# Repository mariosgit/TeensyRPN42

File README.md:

# What ???

Trying to compile Free42 on a Teensy4 / STM32F4xx.

It's a PlatformIO project, copied some code from free42 into lib and trying to compile it...

Allmost, just some link references to open/unlink/link file operations triggered from somethere ???

# Status

Ultraexperimental.

Works with double precision over terminal.

```
╒══════════════════════════════════════════════════════════════════════════════════════════════════════════════════╕
│                                                                                                                  │
│                                                                                                                  │
│             ▄▀▀▀▄       ▄▀▀▀▄ ▄▀▀▀▄ ▄▀▀▀▄ ▀▀▀▀█  ▄█   ▀▀▀▀█ ▄▀▀▀▄   ▄█  ▀▀▀▀█ ▄▀▀▀▄ ▄▀▀▀▄ ▄▄▄▄         ▄█        │
│ ▀▄ ▄▀ ▄       ▄▄▀       ▀▄▄▄█   ▄▄▀  ▄▄▄▀   ▄▀    █     ▄▀  █ ▄▀█ ▄▀ █    ▄▀    ▄▄▀  ▄▄▄▀ █▄▄   ▄▄▄▄    █        │
│   █   ▄     ▄▀     ▄▄      ▄▀ ▄▀    ▄   █  █      █    █    █▀  █ ▀▀▀█▀  █    ▄▀    ▄   █ █▄▄▄          █        │
│   ▀         ▀▀▀▀▀  ▀▀    ▀▀   ▀▀▀▀▀  ▀▀▀   ▀     ▀▀▀   ▀     ▀▀▀     ▀   ▀    ▀▀▀▀▀  ▀▀▀               ▀▀▀       │
│                    ▄█         ▀▀▀▀█ █▀▀▀▀  ▄▀▀  ▄▀▀▀▄ ▀▀▀▀█ ▄▀▀▀▄ █▀▀▀▀ █▀▀▀▀ ▄▀▀▀▄  ▄█   ▀▀▀▀█ ▄▄▄▄         ▄█  │
│ ▀▄ ▄▀ ▄     ▄▄▄▄    █           ▄▀  ▀▀▀▀▄ █▄▄▄   ▄▄▄▀   ▄▀   ▄▄▄▀ ▀▀▀▀▄ ▀▀▀▀▄ ▀▄▄▄▀   █     ▄▀  █▄▄   ▄▄▄▄    █  │
│  ▄▀▄  ▄             █    ▄▄    █    ▄   █ █   █ ▄   █  █    ▄   █ ▄   █ ▄   █ █   █   █    █    █▄▄▄          █  │
│ ▀   ▀              ▀▀▀   ▀▀    ▀     ▀▀▀   ▀▀▀   ▀▀▀   ▀     ▀▀▀   ▀▀▀   ▀▀▀   ▀▀▀   ▀▀▀   ▀                 ▀▀▀ │
╘══════════════════════════════════════════════════════════════════════════════════════════════════════════════════╛
```

# Software

* replaced scanf %e %g with own parser.
  * Todo: PIO_FRAMEWORK_ARDUINO_NANOLIB_FLOAT_SCANF ([from platformio stm32 page](https://docs.platformio.org/en/latest/platforms/ststm32.html))

* quad precission ?
  * checking free42(swissmicro build process..)
    * gcc111libbid-arm64.a - lib src is packaged with it. And available on github
    * there is scanf stuff in ```common/core_phloat.cc``` only when not ARM build ?
    * cmd line:
    ```
    arm-none-eabi-g++ -Os -DDM42_OLDHW -I../common -DRELEASE -MMD -Wall -Wno-misleading-indentation -Wno-parentheses -Wno-write-strings -Wno-maybe-uninitialized -Wno-unknown-pragmas -Wno-class-memaccess -Wno-sign-compare -fno-exceptions -fno-rtti -DVERSION="\"3.3.8\"" -DDECIMAL_CALL_BY_REFERENCE=1 -DDECIMAL_GLOBAL_ROUNDING=1 -DDECIMAL_GLOBAL_ROUNDING_ACCESS_FUNCTIONS=1 -DDECIMAL_GLOBAL_EXCEPTION_FLAGS=1 -DDECIMAL_GLOBAL_EXCEPTION_FLAGS_ACCESS_FUNCTIONS=1 -D_WCHAR_T_DEFINED  -fdata-sections -ffunction-sections -Wl,--gc-sections -ggdb -mthumb -march=armv7e-m -mfloat-abi=hard -mfpu=fpv4-sp-d16 -DARM -DBCD_MATH -c -o core_phloat.o ../common/core_phloat.cc
    ```

  * It builds with the intel lib but it's a bit (way too) large
    ```
    ld: region `RAM' overflowed by 798408 bytes
    ld: region `FLASH' overflowed by 2006716 bytes
    ```

# Hardware

Ideas...

* STM32 ? Nucleo-F411RE - is dev board 
  ```
  RAM:   [=         ]   9.7% (used 12704 bytes from 131072 bytes)
  Flash: [======    ]  62.7% (used 328636 bytes from 524288 bytes)
  ```
  Connect other board to Nucleo STLink programmer part:
  * Remove SB13/SB14 for TX/RX connection to Nucleo MCU
  * Connect SWD (SWO not needed) (Open Jumpers to Nucleo MCU)
  * Connect TX->RX Rx->TX

  Alternative ? L432KC ?
* Display ???
  * OLED ? 256x64
* Keys 
  * K.Choc low profile mechaniks
* Power ?
  * Single Lipo ? Cheap Charger...

## PCB Ordered 

commit: 9db91b7e23bbdf1880c24b6f514a0bee10d9d54c

## Costa ?

| What | Where | $$$ |
|---|---|---:|
| PCB | JLC 5x | 27/5 = 5.4 |
| OLED "OLED Display 2.8" 256*64" | AliEx | 22 |
| Keith Choc V1 | AliEx | ~30 |
| LEDs "WS2812 2020" 500x | AliEx | 22/13 = 1.7 |
| BOM all | Reichelt | 20 |
| **Sum** | | ~100 |

# Refs

thomasokken's ingenious https://thomasokken.com/free42 https://github.com/aswild/free42

And code on github: https://github.com/swissmicros/free42

OpenRPNCalc ? on github, uses CubeIDE 🤯 and own code..

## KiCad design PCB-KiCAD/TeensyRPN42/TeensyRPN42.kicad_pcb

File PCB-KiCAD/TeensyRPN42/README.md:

# TeensyRPN42 – PCB

Main board for an RPN calculator running [Free42](https://thomasokken.com/free42/) on an STM32F405.
37 Kailh Choc V1 keys, each with an SK6805 RGB LED in the key window, a 2.8" 256×64 SPI OLED, and a LiPo
supply with a switchable 5 V boost for the LEDs. Two layers; all parts on the top side except the SWD (J1) and serial (J4) headers.

| Front | Headers | Back |
|---|---|---|
|  |  |  |
|  | |  |

**Interactive BOM:** [bom/TeensyRPN42_ibom.html](bom/TeensyRPN42_ibom.html) (open in a browser; placement per part, with Reichelt numbers).

## Specs

| | |
|---|---|
| Board | 113.0 × 184.1 mm, 3 mm corner radius, 2 layers, 4 × M3 mounting holes (3.7 mm, tolerance for the OLED module) |
| Fab | AISLER 2-layer simple (min. track 0.2 mm, clearance 0.15 mm, via 0.7/0.3 mm), vias tented |
| MCU | STM32F405RGT6 (LQFP64), 8 MHz HSE (Y3, ceramic 5.2 × 3.4 mm), 32.768 kHz LSE (Y2) for the RTC |
| Display | 2.8" OLED module, 16-pin header J3, SPI1 |
| Keys | 37 × Choc V1 (1u / 1.25u / 2u ENTER), 7 × 6 matrix, no diodes |
| LEDs | 38 × SK6805 2020 (2 × 2 mm, on the 2427 footprint; two under the 2u ENTER), one data chain, 5 V via 74AHCT125 level shifter |
| Power | 1-cell LiPo through an off-board TP4056 + DW01 module (J5 BAT, J9 CHG Vusb) |
| 3.3 V | MCP1727-3302 LDO from the battery (MCU, OLED) |
| 5 V | TS1935BCX5 boost (2.6–5.5 V in, 1.9 A switch), switched by PC3 through a P-FET load switch |
| USB | Micro-USB (J7), USB FS on PA11/PA12, USBLC6 ESD, 750 mA PTC, SMAJ5.0A TVS |
| Programming | USB DFU (BOOT0 button / jumper), SWD (J1) |

## Connectors

| Ref | Side | Pins |
|---|---|---|
| J1 SWD | back | 1 3V3 (VTref) · 2 SWCLK · 3 GND · 4 SWDIO · 5 NRST · 6 SWO |
| J4 Serial | back | GND · TX (PA2) · RX (PA3), 3.3 V, 115200 baud |
| J5 BAT | top edge | 1 GND · 2 PWR_SYS ← TP4056 module OUT+/OUT− (never B−) |
| J9 CHG Vusb | top edge | 1 GND · 2 VBUS → TP4056 module IN+/IN− |
| J10 BOOT0 | top | jumper = BOOT0 to 3.3 V → every reset lands in DFU |
| J2 / J8 | top | I²C1: PB8 SCL, PB9 SDA, 2.2 k pull-ups (mini OLED / spare) |
| J3 | top | 2.8" OLED module (SPI1) |
| J7 | top edge | Micro-USB (data + charging) |
| SW1 / SW2 | top (right / left edge) | RESET / BOOT0 |

## MCU pin map

| Function | Pins |
|---|---|
| Matrix rows 1…7 | PA9, PA10, PD2, PC12, PC11, PC10, PA15 |
| Matrix columns 0…5 | PC7, PC8, PC9, PB5, PB6, PB7 (inputs, pull-up) |
| OLED (SPI1) | PA5 SCK, PA7 MOSI, PA4 CS, PC4 D/C, RESET = NRST |
| LED data | PB10 → 74AHCT125 → 470 Ω → D1 … D38 |
| I²C1 | PB8 SCL, PB9 SDA |
| USART2 | PA2 TX, PA3 RX |
| USB FS | PA11 D−, PA12 D+ (VBUS sensing off, PA9 is ROW1) |
| SWD | PA13 SWDIO, PA14 SWCLK, PB3 SWO |
| VBUS_DET | PA1, 100 k / 150 k divider → ≈ 3.0 V with USB |
| BAT_SENSE | PA0, 200 k / 200 k divider → V_bat / 2 |
| BOOST_EN | PC3, high = 5 V on (100 k pull-down, off during reset) |
| BOOT0 / BOOT1 | BOOT0 10 k pull-down (SW2 / J10 → 3.3 V), PB2 10 k pull-down |
| Spare | PA8, PB0, PB1, PB4, PB11, PB12–PB15, PC0, PC1, PC2, PC5, PC6, PC13 |

## BOM

Full BOM with your Part-DB stock and the Reichelt order list: **[bom/BOM.md](bom/BOM.md)**.

- Resistors, 100 nF, 1 nF, 18 pF, the STM32F405 and the OLED come from stock.
- Reichelt: 22 positions, about 8.60 € (ICs, FETs, ferrites, 22 µF, PTC, TVS, Schottky, crystal Y3 (IC14M8), DTSM-61K, MIC USB BBU, headers).
- L4: Reichelt `L-242418FPS 6,3µ` (6.3 µH, Isat 3.8 A) on the SRP5030 pads; L5 (DNP) is a parallel 10 × 10 mm footprint for the stock SRU1048-100Y.
- Elsewhere: Y2 (32.768 kHz 3215, CL 6–7 pF), 38 SK6805 2020 LEDs (ordered).
- Own stock: 37 Kailh Choc V1 switches; keycaps are 3D printed (`KeycapsForKailhChoc-files/`).

**DNP (footprint only):** L5 (10 × 10 mm alternative to L4), Y1 (alternative 8 MHz HC49 footprint),
Y4 (alternative 32.768 kHz footprint, fits the Reichelt IQD LFXTAL003000).
**Off-board:** TP4056 + DW01 charger module (set R_PROG to 2.4 k ≈ 500 mA), 1-cell LiPo.

## Design notes

- **Power path:** battery → module OUT+ → J5 → PWR_SYS. PWR_SYS feeds the LDO (always on) and the boost
  through Q1. BOOST_EN (PC3) high → Q2 pulls Q1's gate low → BOOST_IN = battery → U5 starts → +5 V.
  R24 10 k + C56 100 nF slow Q1's turn-on to ≈ 0.9 ms (inrush into the 5 V / LED caps).
  Q1 is needed because a non-synchronous boost always conducts battery → L4 → D42 → +5 V; without it the
  LEDs would draw idle current in soft-off.
- **5 V budget:** ≈ 0.6 A at 5 V from a 3.0 V battery. Limit LED brightness in firmware (total LED current
  ≲ 0.5 A). Soft-off / low-battery warning at ≈ 3.4 V (BAT_SENSE); the DW01 only cuts at ≈ 2.5 V.
- **V-LED:** separate branch behind ferrite L3 with C53 22 µF at the feed point and 24 × 100 nF spread along the rows.
  Ladder layout: one trunk on each side, one bus per key row, so most rows are fed from both ends.
- **Filtering:** L1 + C6/C30 for VDDA, L2 + C13 for the OLED supply.
- **Key matrix (no diodes):** drive only the active row low, all other rows hi-Z; columns are inputs with
  pull-ups. One or two keys at a time are reliable; ghosting needs three or more held keys.
- **DFU:** hold BOOT0 (SW2), tap RESET (SW1), release. During development, a jumper on J10 keeps the board
  in DFU after every reset. `dfu-util -a 0 -s 0x08000000:leave -D firmware.bin`.
- **Clock:** use HSE 8 MHz → PLL 168 MHz (PLLM 8, PLLN 336, PLLP 2, PLLQ 7 = 48 MHz USB); HSI is not
  accurate enough for USB.
- **Fixed mechanics:** OLED J3, the 37 switches, H1–H4 and the outline are locked;
  `python3 check_fixed.py` verifies them against `fixed_placement.json`.
- **DRC:** clean. The LED-in-switch courtyard overlaps (intended) and H3/H4 vs J3 are excluded. Footprint
  library-mismatch warnings are local edits (silk tweaks) and intentional.

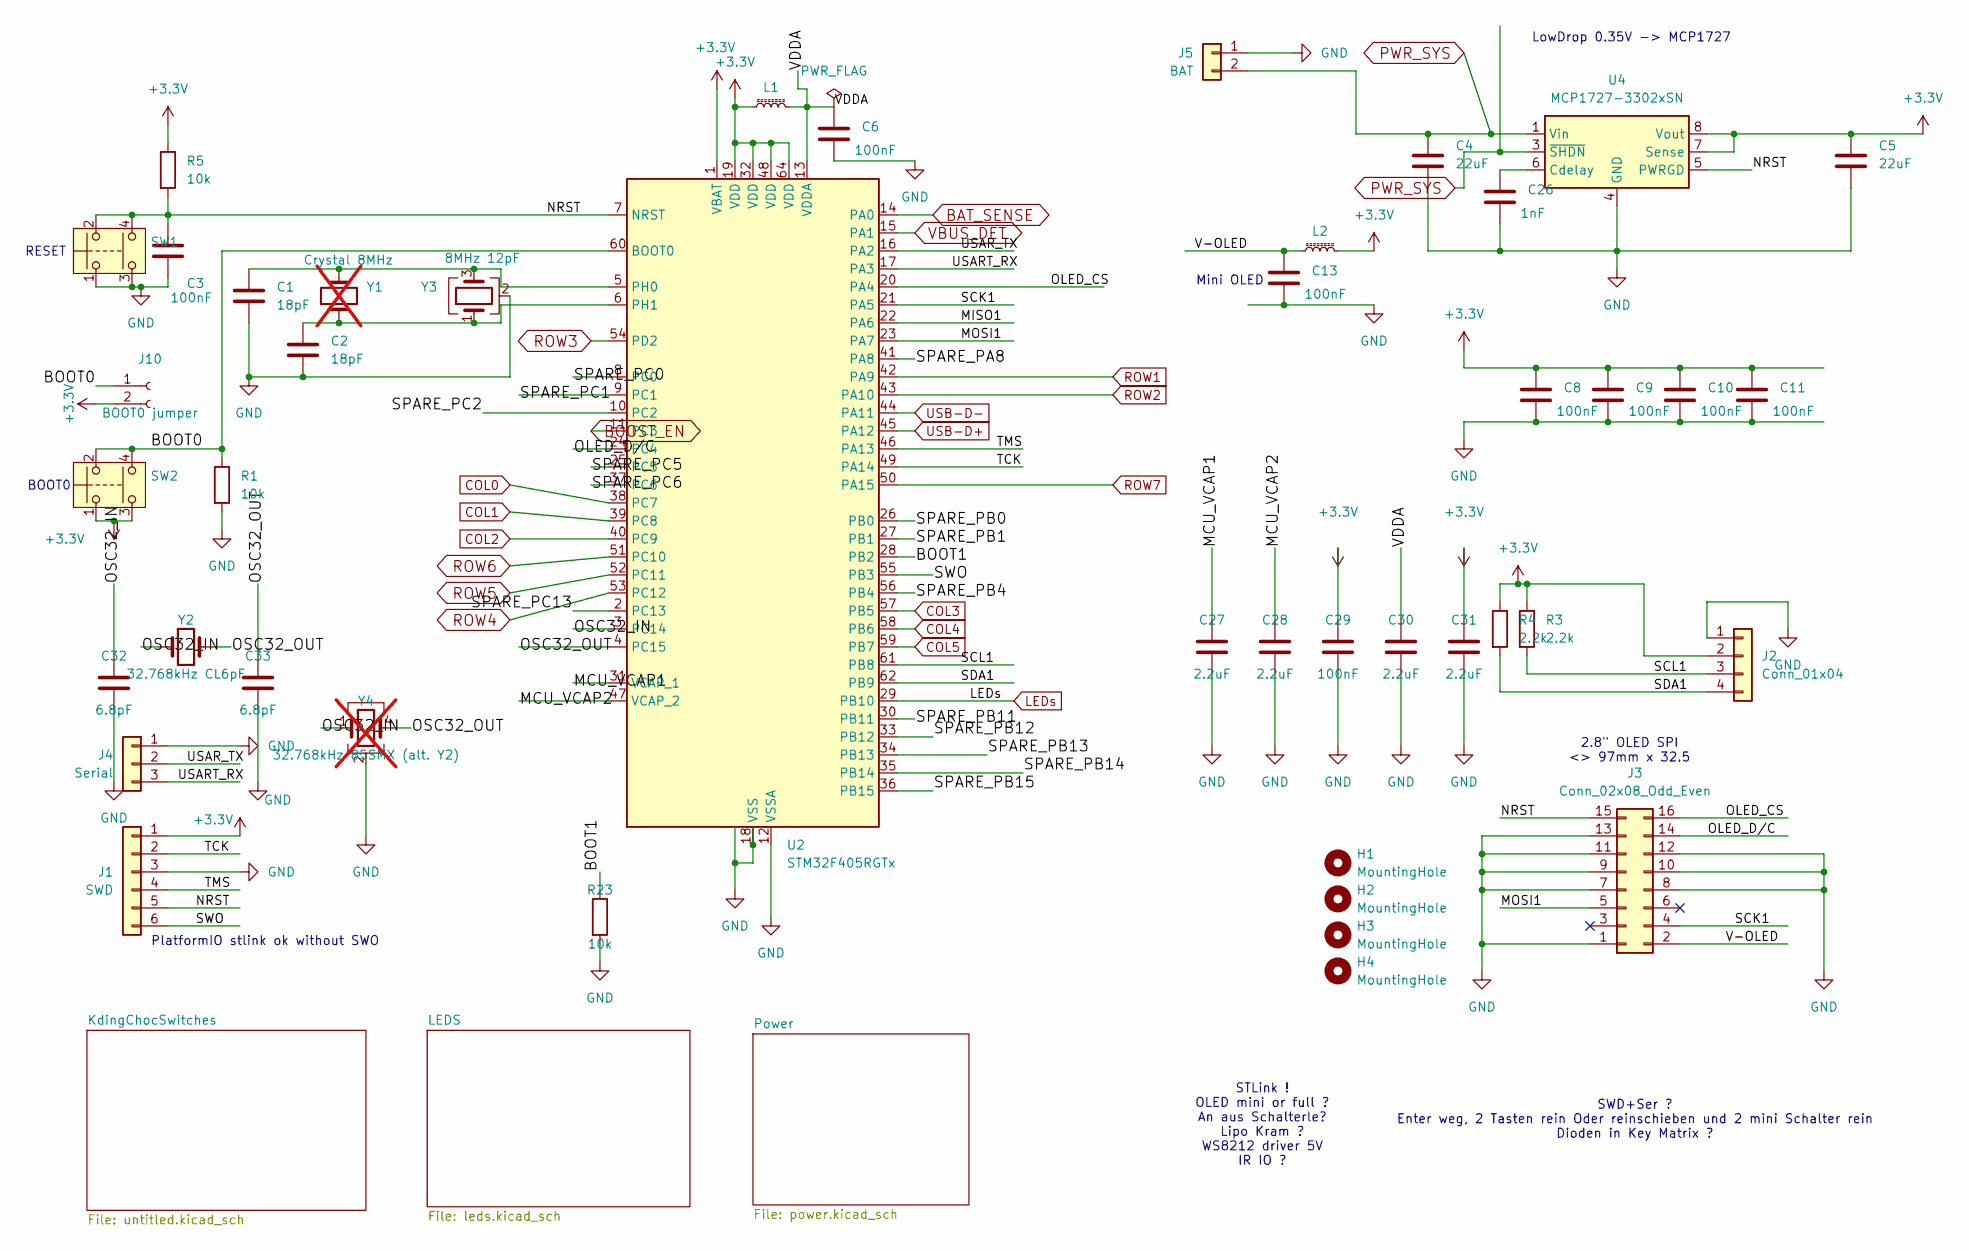
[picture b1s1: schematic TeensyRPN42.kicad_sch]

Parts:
C1, C2: 18pF; C_0603_1608Metric_Pad1.08x0.95mm_HandSolder
C3, C6, C8, C9, C10, C11, C13, C29: 100nF; C_0603_1608Metric_Pad1.08x0.95mm_HandSolder
C4, C5: 22uF; C_1206_3216Metric_Pad1.33x1.80mm_HandSolder
C26: 1nF; C_0603_1608Metric_Pad1.08x0.95mm_HandSolder
C27, C28, C30, C31: 2.2uF; C_0603_1608Metric_Pad1.08x0.95mm_HandSolder
C32, C33: 6.8pF; C_0603_1608Metric_Pad1.08x0.95mm_HandSolder
H1, H2, H3, H4: MountingHole; MountingHole_3.7mm
J1: SWD; PinHeader_1x06_P2.54mm_Vertical
J2: Conn_01x04; PinSocket_1x04_P2.54mm_Vertical
J3: Conn_02x08_Odd_Even; OLED-2.8inch16pin
J4: Serial; PinHeader_1x03_P2.54mm_Vertical
J5: BAT; JST_EH_S2B-EH_1x02_P2.50mm_Horizontal
J10: BOOT0 jumper; PinHeader_1x02_P2.54mm_Vertical
L1: 600R@100MHz 0.5A; L_0603_1608Metric_Pad1.05x0.95mm_HandSolder
L2: 600R@100MHz 1.3A; L_0603_1608Metric_Pad1.05x0.95mm_HandSolder
R1, R5, R23: 10k; R_0603_1608Metric_Pad0.98x0.95mm_HandSolder
R3, R4: 2.2k; R_0603_1608Metric_Pad0.98x0.95mm_HandSolder
SW1, SW2: SW_Push_Dual; SW_SPST_PTS645Sx43SMTR92
U2: STM32F405RGTx; LQFP-64_10x10mm_P0.5mm
U4: MCP1727-3302xSN; SOIC-8_3.9x4.9mm_P1.27mm
Y1: Crystal 8MHz; Crystal_SMD_HC49-SD; not fitted
Y2: 32.768kHz CL6pF; Crystal_SMD_3215-2Pin_3.2x1.5mm
Y3: 8MHz 12pF; Crystal_SMD_0603-4Pin_6.0x3.5mm_HandSoldering
Y4: 32.768kHz 85SMX (alt. Y2); Crystal_SMD_IQD_85SMX-4Pin_8.7x3.7mm; not fitted

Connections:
+3.3V: C5.1, C8.1, C9.1, C10.1, C11.1, C29.1, C31.1, J1.1, J2.2, J10.2, L1.1, L2.2, R3.1, R4.1, R5.1, SW2.1, SW2.3, U2.1 (VBAT), U2.19 (VDD), U2.32 (VDD), U2.48 (VDD), U2.64 (VDD), U4.7 (Sense), U4.8 (Vout)
/BOOT0: J10.1, R1.1, SW2.2, SW2.4, U2.60 (BOOT0)
/BOOT1: R23.1, U2.28 (PB2)
/MCU_VCAP1: C27.1, U2.31 (VCAP_1)
/MCU_VCAP2: C28.1, U2.47 (VCAP_2)
/MISO1: U2.22 (PA6)
/MOSI1: J3.5, U2.23 (PA7)
/NRST: C3.1, J1.5, J3.15, R5.2, SW1.2, SW1.4, U2.7 (NRST), U4.5 (PWRGD)
/OLED_CS: J3.16, U2.20 (PA4)
/OSC32_IN: C32.1, U2.3 (PC14), Y2.1, Y4.1
/OSC32_OUT: C33.1, U2.4 (PC15), Y2.2, Y4.4
/SCK1: J3.4, U2.21 (PA5)
/SCL1: J2.3, R3.2, U2.61 (PB8)
/SDA1: J2.4, R4.2, U2.62 (PB9)
/SPARE_PA8: U2.41 (PA8)
/SPARE_PB0: U2.26 (PB0)
/SPARE_PB1: U2.27 (PB1)
/SPARE_PB4: U2.56 (PB4)
/SPARE_PB11: U2.30 (PB11)
/SPARE_PB12: U2.33 (PB12)
/SPARE_PB13: U2.34 (PB13)
/SPARE_PB14: U2.35 (PB14)
/SPARE_PB15: U2.36 (PB15)
/SPARE_PC0: U2.8 (PC0)
/SPARE_PC1: U2.9 (PC1)
/SPARE_PC2: U2.10 (PC2)
/SPARE_PC5: U2.25 (PC5)
/SPARE_PC6: U2.37 (PC6)
/SPARE_PC13: U2.2 (PC13)
/SWO: J1.6, U2.55 (PB3)
/TCK: J1.2, U2.49 (PA14)
/TMS: J1.4, U2.46 (PA13)
/USART_RX: J4.3, U2.17 (PA3)
/USAR_TX: J4.2, U2.16 (PA2)
/V-OLED: C13.1, J3.2, L2.1
/VDDA: C6.1, C30.1, L1.2, U2.13 (VDDA)
BAT_SENSE: U2.14 (PA0); also elsewhere on the board
BOOST_EN: U2.11 (PC3); also elsewhere on the board
COL0: U2.38 (PC7); also elsewhere on the board
COL1: U2.39 (PC8); also elsewhere on the board
COL2: U2.40 (PC9); also elsewhere on the board
COL3: U2.57 (PB5); also elsewhere on the board
COL4: U2.58 (PB6); also elsewhere on the board
COL5: U2.59 (PB7); also elsewhere on the board
GND: C1.2, C2.2, C3.2, C4.2, C5.2, C6.2, C8.2, C9.2, C10.2, C11.2, C13.2, C26.2, C27.2, C28.2, C29.2, C30.2, C31.2, C32.2, C33.2, J1.3, J2.1, J3.1, J3.7, J3.8, J3.9, J3.10, J3.11, J3.12, J3.13, J4.1, J5.1, R1.2, R23.2, SW1.1, SW1.3, U2.12 (VSSA), U2.18 (VSS), U2.63 (VSS), U4.4 (GND), Y3.2 (G), Y3.4 (G), Y4.2 (G), Y4.3 (G); also elsewhere on the board
LEDs: U2.29 (PB10); also elsewhere on the board
unnamed: C1.1, U2.5 (PH0), Y1.2, Y3.3
unnamed: C2.1, U2.6 (PH1), Y1.1, Y3.1
unnamed: C26.1, U4.6 (Cdelay)
PWR_SYS: C4.1, J5.2, U4.1 (Vin), U4.2 (Vin), U4.3 (~SHDN); also elsewhere on the board
ROW1: U2.42 (PA9); also elsewhere on the board
ROW2: U2.43 (PA10); also elsewhere on the board
ROW3: U2.54 (PD2); also elsewhere on the board
ROW4: U2.53 (PC12); also elsewhere on the board
ROW5: U2.52 (PC11); also elsewhere on the board
ROW6: U2.51 (PC10); also elsewhere on the board
ROW7: U2.50 (PA15); also elsewhere on the board
USB-D+: U2.45 (PA12); also elsewhere on the board
USB-D-: U2.44 (PA11); also elsewhere on the board
VBUS_DET: U2.15 (PA1); also elsewhere on the board

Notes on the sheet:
SWD+Ser ? Enter weg, 2 Tasten rein Oder reinschieben und 2 mini Schalter rein Dioden in Key Matrix ?
BOOT0
PlatformIO stlink ok without SWO
RESET
2.8" OLED SPI <> 97mm x 32.5
Mini OLED
STLink ! OLED mini or full ? An aus Schalterle? Lipo Kram ? WS8212 driver 5V IR IO ?
LowDrop 0.35V -> MCP1727

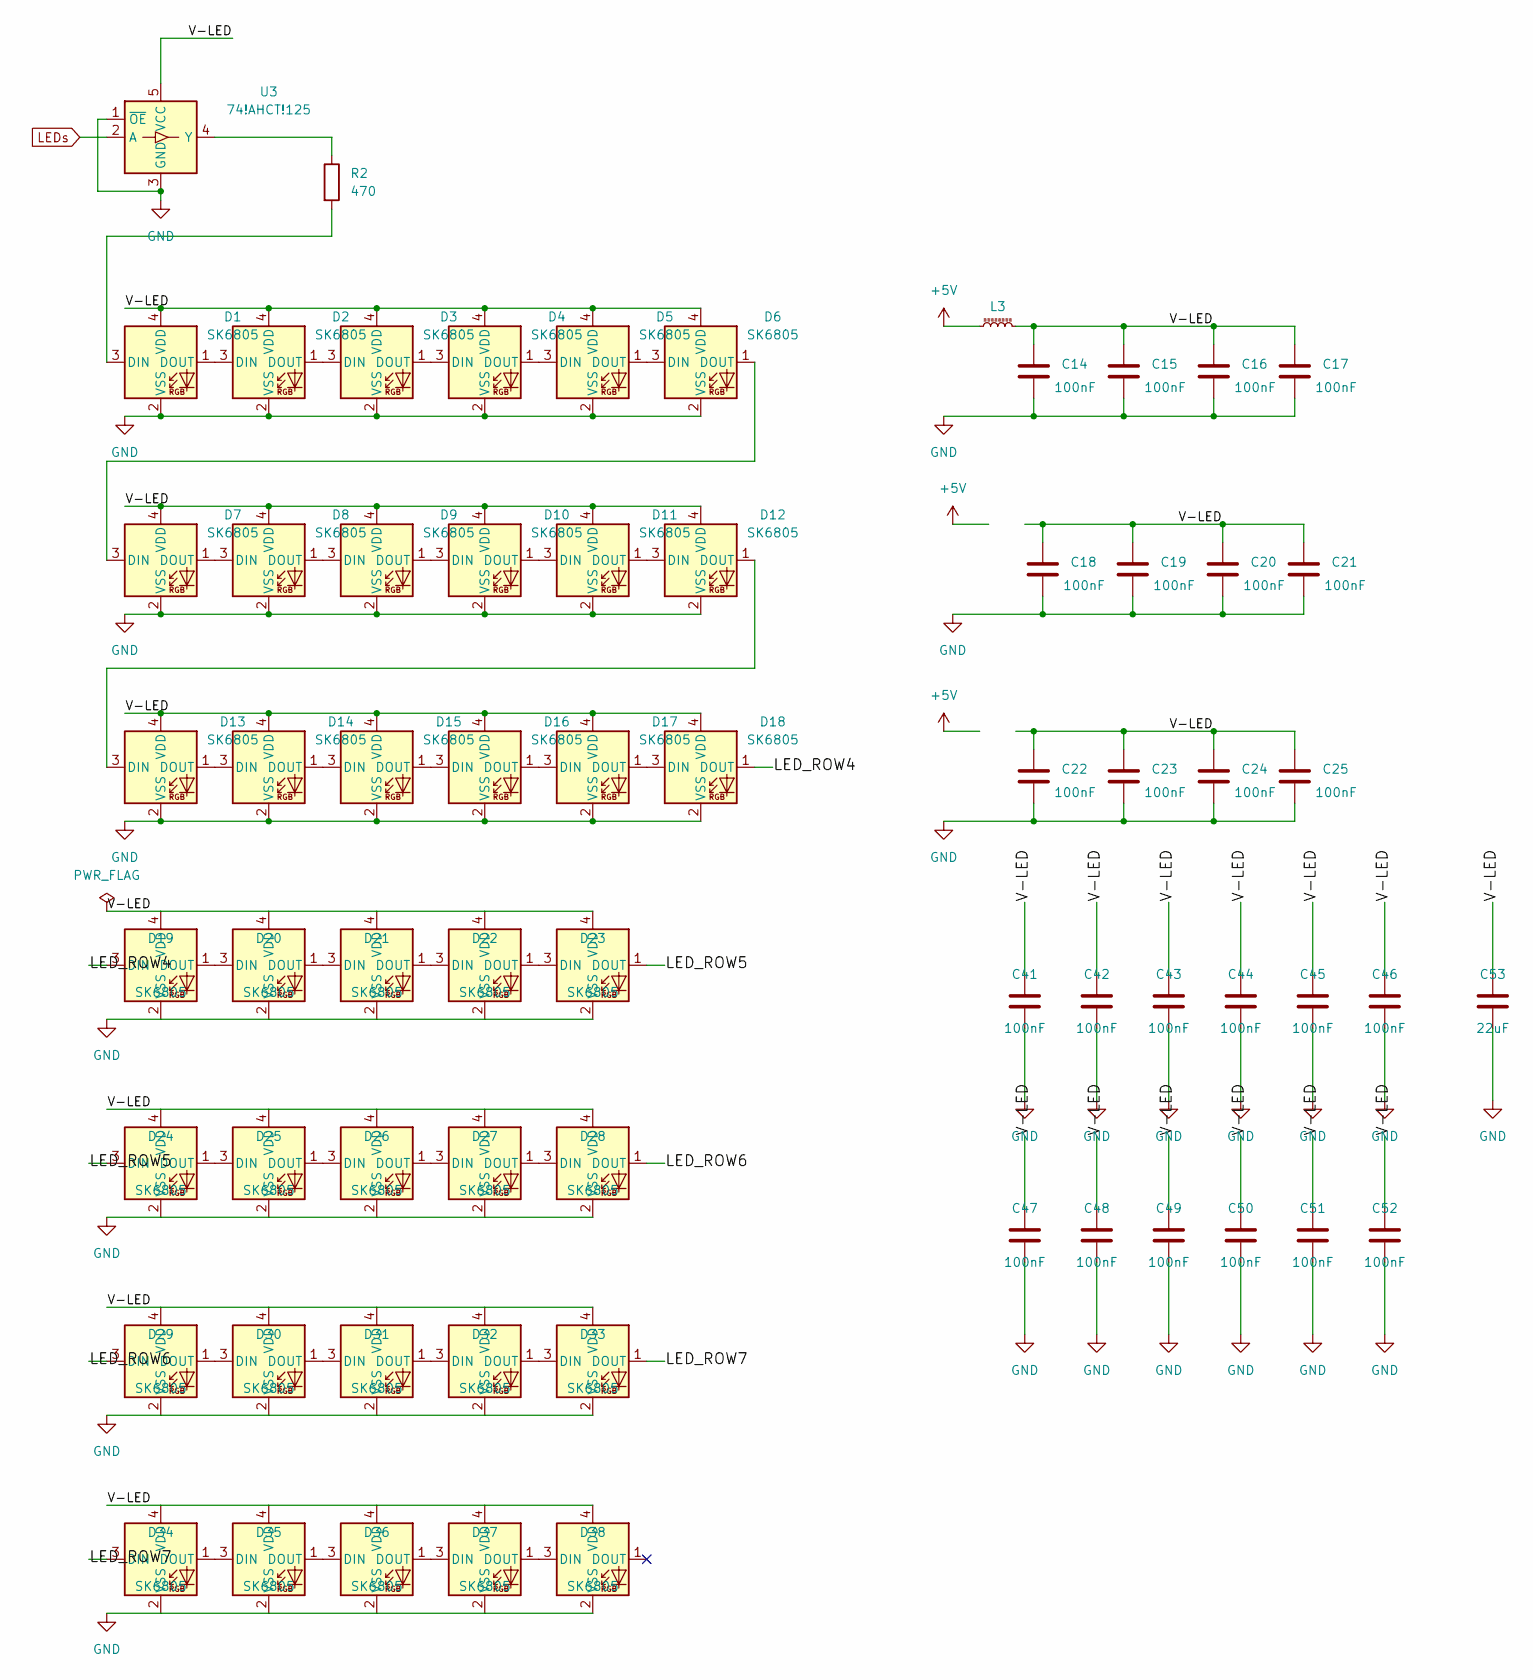
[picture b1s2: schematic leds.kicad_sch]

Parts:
C14, C15, C16, C17, C18, C19, C20, C21, C22, C23, C24, C25, C41, C42, C43, C44, C45, C46, C47, C48, C49, C50, C51, C52: 100nF; C_0603_1608Metric_Pad1.08x0.95mm_HandSolder
C53: 22uF; C_1206_3216Metric_Pad1.33x1.80mm_HandSolder
D1, D2, D3, D4, D5, D6, D7, D8, D9, D10, D11, D12, D13, D14, D15, D16, D17, D18, D19, D20, D21, D22, D23, D24, D25, D26, D27, D28, D29, D30, D31, D32, D33, D34, D35, D36, D37, D38: SK6805; LED_SK6805_PLCC4_2.4x2.7mm_P1.3mm
L3: 600R@100MHz 1.3A; L_0603_1608Metric_Pad1.05x0.95mm_HandSolder
R2: 470; R_0603_1608Metric_Pad0.98x0.95mm_HandSolder
U3: 74!AHCT!125; SOT-353_SC-70-5

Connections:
+5V: L3.1; also elsewhere on the board
/LEDS/LED_ROW4: D18.1 (DOUT), D19.3 (DIN)
/LEDS/LED_ROW5: D23.1 (DOUT), D24.3 (DIN)
/LEDS/LED_ROW6: D28.1 (DOUT), D29.3 (DIN)
/LEDS/LED_ROW7: D33.1 (DOUT), D34.3 (DIN)
/LEDS/V-LED: C14.1, C15.1, C16.1, C17.1, C18.1, C19.1, C20.1, C21.1, C22.1, C23.1, C24.1, C25.1, C41.1, C42.1, C43.1, C44.1, C45.1, C46.1, C47.1, C48.1, C49.1, C50.1, C51.1, C52.1, C53.1, D1.4 (VDD), D2.4 (VDD), D3.4 (VDD), D4.4 (VDD), D5.4 (VDD), D6.4 (VDD), D7.4 (VDD), D8.4 (VDD), D9.4 (VDD), D10.4 (VDD), D11.4 (VDD), D12.4 (VDD), D13.4 (VDD), D14.4 (VDD), D15.4 (VDD), D16.4 (VDD), D17.4 (VDD), D18.4 (VDD), D19.4 (VDD), D20.4 (VDD), D21.4 (VDD), D22.4 (VDD), D23.4 (VDD), D24.4 (VDD), D25.4 (VDD), D26.4 (VDD), D27.4 (VDD), D28.4 (VDD), D29.4 (VDD), D30.4 (VDD), D31.4 (VDD), D32.4 (VDD), D33.4 (VDD), D34.4 (VDD), D35.4 (VDD), D36.4 (VDD), D37.4 (VDD), D38.4 (VDD), L3.2, U3.5 (VCC)
GND: C14.2, C15.2, C16.2, C17.2, C18.2, C19.2, C20.2, C21.2, C22.2, C23.2, C24.2, C25.2, C41.2, C42.2, C43.2, C44.2, C45.2, C46.2, C47.2, C48.2, C49.2, C50.2, C51.2, C52.2, C53.2, D1.2 (VSS), D2.2 (VSS), D3.2 (VSS), D4.2 (VSS), D5.2 (VSS), D6.2 (VSS), D7.2 (VSS), D8.2 (VSS), D9.2 (VSS), D10.2 (VSS), D11.2 (VSS), D12.2 (VSS), D13.2 (VSS), D14.2 (VSS), D15.2 (VSS), D16.2 (VSS), D17.2 (VSS), D18.2 (VSS), D19.2 (VSS), D20.2 (VSS), D21.2 (VSS), D22.2 (VSS), D23.2 (VSS), D24.2 (VSS), D25.2 (VSS), D26.2 (VSS), D27.2 (VSS), D28.2 (VSS), D29.2 (VSS), D30.2 (VSS), D31.2 (VSS), D32.2 (VSS), D33.2 (VSS), D34.2 (VSS), D35.2 (VSS), D36.2 (VSS), D37.2 (VSS), D38.2 (VSS), U3.1 (~OE), U3.3 (GND); also elsewhere on the board
LEDs: U3.2 (A); also elsewhere on the board
unnamed: D1.3 (DIN), R2.2
unnamed: D1.1 (DOUT), D2.3 (DIN)
unnamed: D2.1 (DOUT), D3.3 (DIN)
unnamed: D3.1 (DOUT), D4.3 (DIN)
unnamed: D4.1 (DOUT), D5.3 (DIN)
unnamed: D5.1 (DOUT), D6.3 (DIN)
unnamed: D6.1 (DOUT), D7.3 (DIN)
unnamed: D7.1 (DOUT), D8.3 (DIN)
unnamed: D8.1 (DOUT), D9.3 (DIN)
unnamed: D9.1 (DOUT), D10.3 (DIN)
unnamed: D10.1 (DOUT), D11.3 (DIN)
unnamed: D11.1 (DOUT), D12.3 (DIN)
unnamed: D12.1 (DOUT), D13.3 (DIN)
unnamed: D13.1 (DOUT), D14.3 (DIN)
unnamed: D14.1 (DOUT), D15.3 (DIN)
unnamed: D15.1 (DOUT), D16.3 (DIN)
unnamed: D16.1 (DOUT), D17.3 (DIN)
unnamed: D17.1 (DOUT), D18.3 (DIN)
unnamed: D19.1 (DOUT), D20.3 (DIN)
unnamed: D20.1 (DOUT), D21.3 (DIN)
unnamed: D21.1 (DOUT), D22.3 (DIN)
unnamed: D22.1 (DOUT), D23.3 (DIN)
unnamed: D24.1 (DOUT), D25.3 (DIN)
unnamed: D25.1 (DOUT), D26.3 (DIN)
unnamed: D26.1 (DOUT), D27.3 (DIN)
unnamed: D27.1 (DOUT), D28.3 (DIN)
unnamed: D29.1 (DOUT), D30.3 (DIN)
unnamed: D30.1 (DOUT), D31.3 (DIN)
unnamed: D31.1 (DOUT), D32.3 (DIN)
unnamed: D32.1 (DOUT), D33.3 (DIN)
unnamed: D34.1 (DOUT), D35.3 (DIN)
unnamed: D35.1 (DOUT), D36.3 (DIN)
unnamed: D36.1 (DOUT), D37.3 (DIN)
unnamed: D37.1 (DOUT), D38.3 (DIN)
unnamed: R2.1, U3.4 (Y)

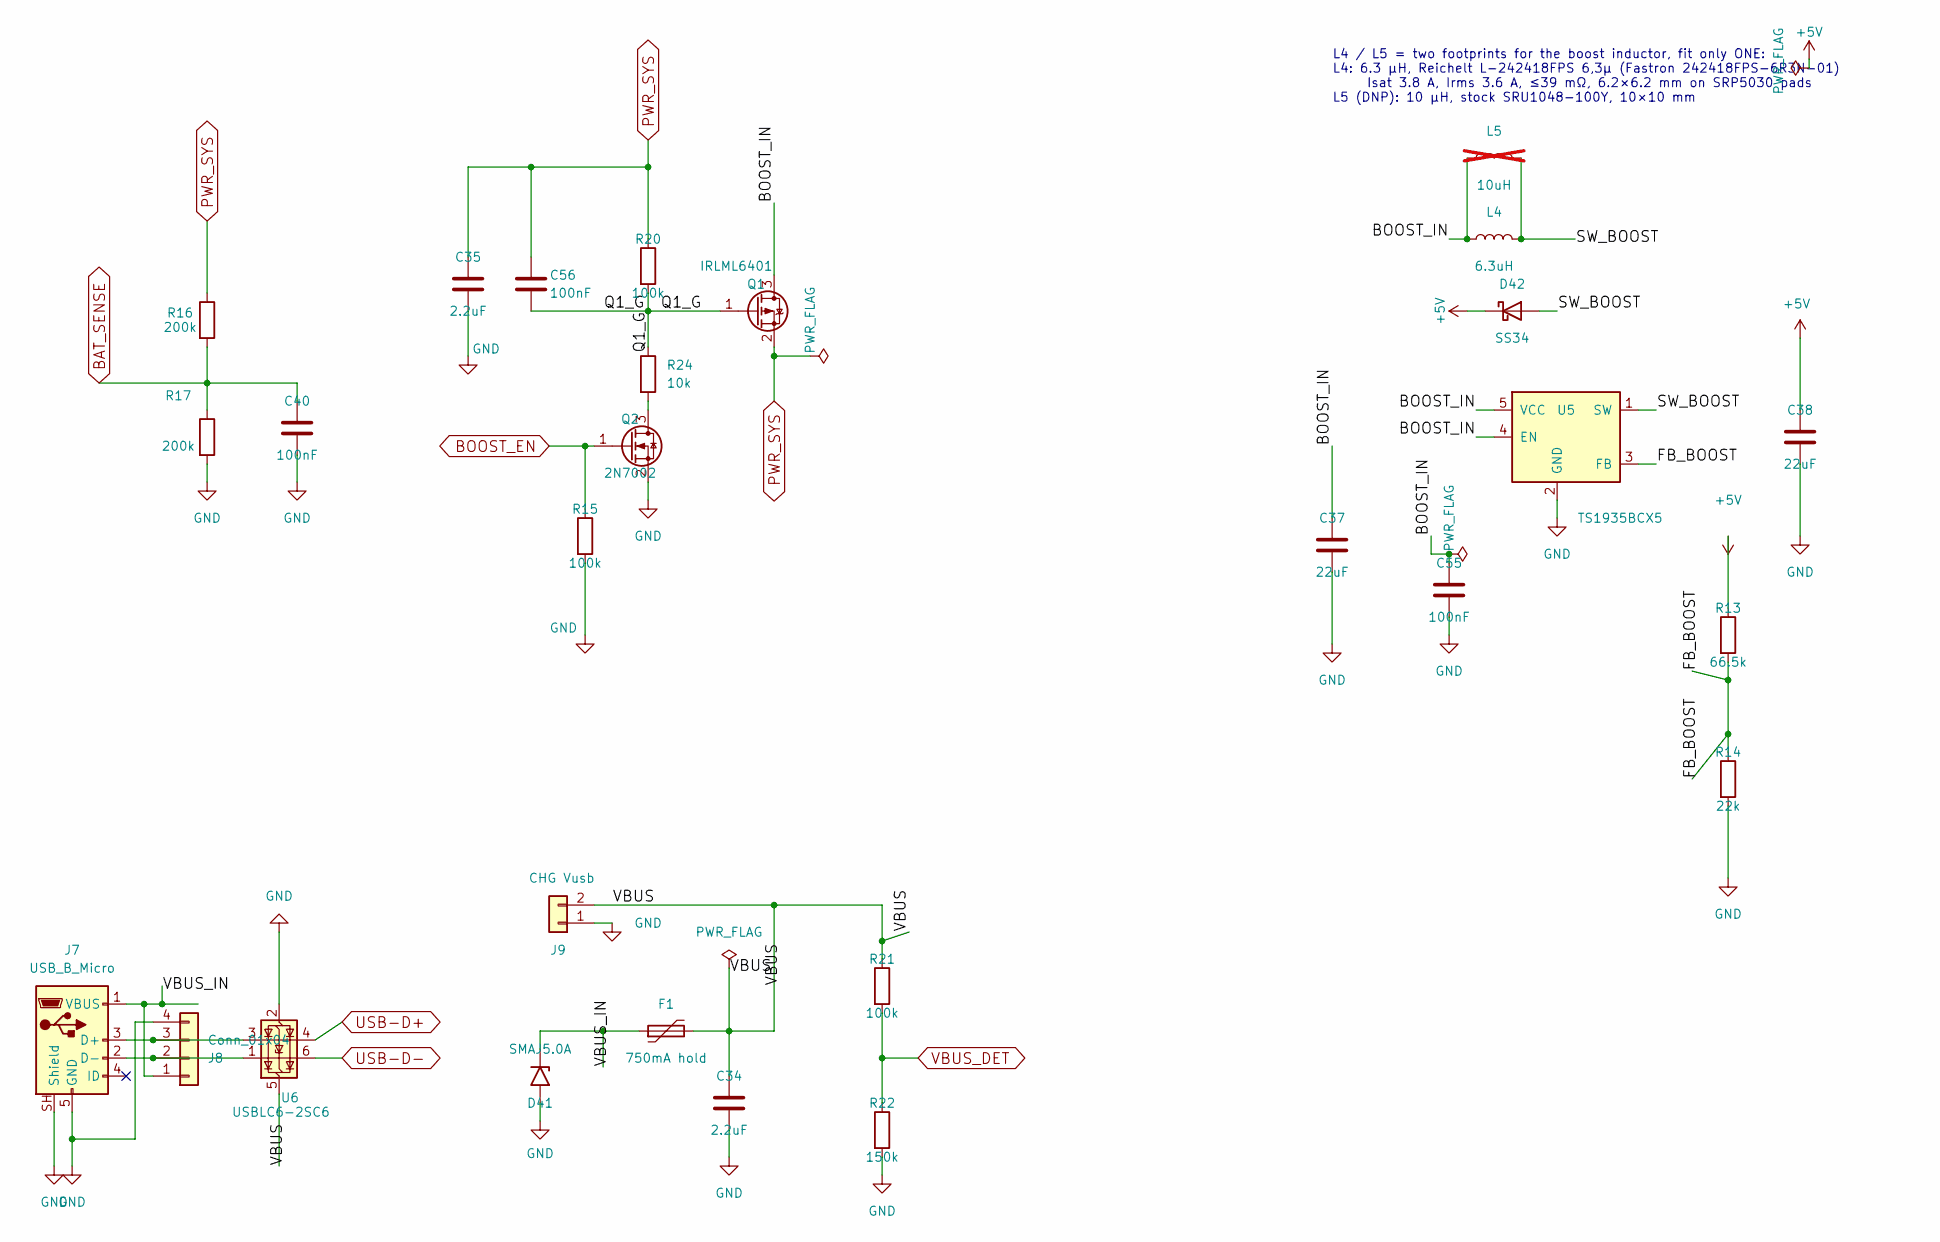
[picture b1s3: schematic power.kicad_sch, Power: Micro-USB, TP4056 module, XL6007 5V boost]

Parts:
C34, C35: 2.2uF; C_0603_1608Metric_Pad1.08x0.95mm_HandSolder
C37, C38: 22uF; C_1206_3216Metric_Pad1.33x1.80mm_HandSolder
C40, C55, C56: 100nF; C_0603_1608Metric_Pad1.08x0.95mm_HandSolder
D41: SMAJ5.0A; D_SMA
D42: SS34; D_SMA
F1: 750mA hold; Fuse_1206_3216Metric
J7: USB_B_Micro; USB_Micro-B_Reichelt_MIC-USB-BBU
J8: Conn_01x04; PinSocket_1x04_P2.54mm_Vertical
J9: CHG Vusb; JST_EH_S2B-EH_1x02_P2.50mm_Horizontal
L4: 6.3uH; L_Bourns_SRP5030T
L5: 10uH; L_Bourns-SRU1028_10.0x10.0mm; not fitted
Q1: IRLML6401; SOT-23
Q2: 2N7002; SOT-23
R13: 66.5k; R_0603_1608Metric_Pad0.98x0.95mm_HandSolder
R14: 22k; R_0603_1608Metric_Pad0.98x0.95mm_HandSolder
R15, R20, R21: 100k; R_0603_1608Metric_Pad0.98x0.95mm_HandSolder
R16, R17: 200k; R_0603_1608Metric_Pad0.98x0.95mm_HandSolder
R22: 150k; R_0603_1608Metric_Pad0.98x0.95mm_HandSolder
R24: 10k; R_0603_1608Metric_Pad0.98x0.95mm_HandSolder
U5: TS1935BCX5; SOT-23-5
U6: USBLC6-2SC6; SOT-23-6

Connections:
+5V: C38.1, D42.1 (K), R13.1; also elsewhere on the board
/Power/BOOST_IN: C37.1, C55.1, L4.1, L5.1, Q1.3 (D), U5.4 (EN), U5.5 (VCC)
/Power/FB_BOOST: R13.2, R14.1, U5.3 (FB)
/Power/Q1_G: C56.2, Q1.1 (G), R20.2, R24.1
/Power/SW_BOOST: D42.2 (A), L4.2, L5.2, U5.1 (SW)
/Power/VBUS: C34.1, F1.2, J9.2, R21.1, U6.5 (VBUS)
/Power/VBUS_IN: D41.1 (A1), F1.1, J7.1 (VBUS), J8.1
BAT_SENSE: C40.1, R16.2, R17.1; also elsewhere on the board
BOOST_EN: Q2.1 (G), R15.1; also elsewhere on the board
GND: C34.2, C35.2, C37.2, C38.2, C40.2, C55.2, D41.2 (A2), J7.5 (GND), J7.SH (Shield), J8.4, J9.1, Q2.2 (S), R14.2, R15.2, R17.2, R22.2, U5.2 (GND), U6.2 (GND); also elsewhere on the board
unnamed: J7.3 (D+), J8.3, U6.3 (I/O2)
unnamed: J7.2 (D-), J8.2, U6.1 (I/O1)
unnamed: Q2.3 (D), R24.2
PWR_SYS: C35.1, C56.1, Q1.2 (S), R16.1, R20.1; also elsewhere on the board
USB-D+: U6.4 (I/O2); also elsewhere on the board
USB-D-: U6.6 (I/O1); also elsewhere on the board
VBUS_DET: R21.2, R22.1; also elsewhere on the board

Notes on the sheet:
L4 / L5 = two footprints for the boost inductor, fit only ONE: L4: 6.3 µH, Reichelt L-242418FPS 6,3µ (Fastron 242418FPS-6R3N-01) Isat 3.8 A, Irms 3.6 A, ≤39 mΩ, 6.2×6.2 mm on SRP5030 pads L5 (DNP): 10 µH, stock SRU1048-100Y, 10×10 mm

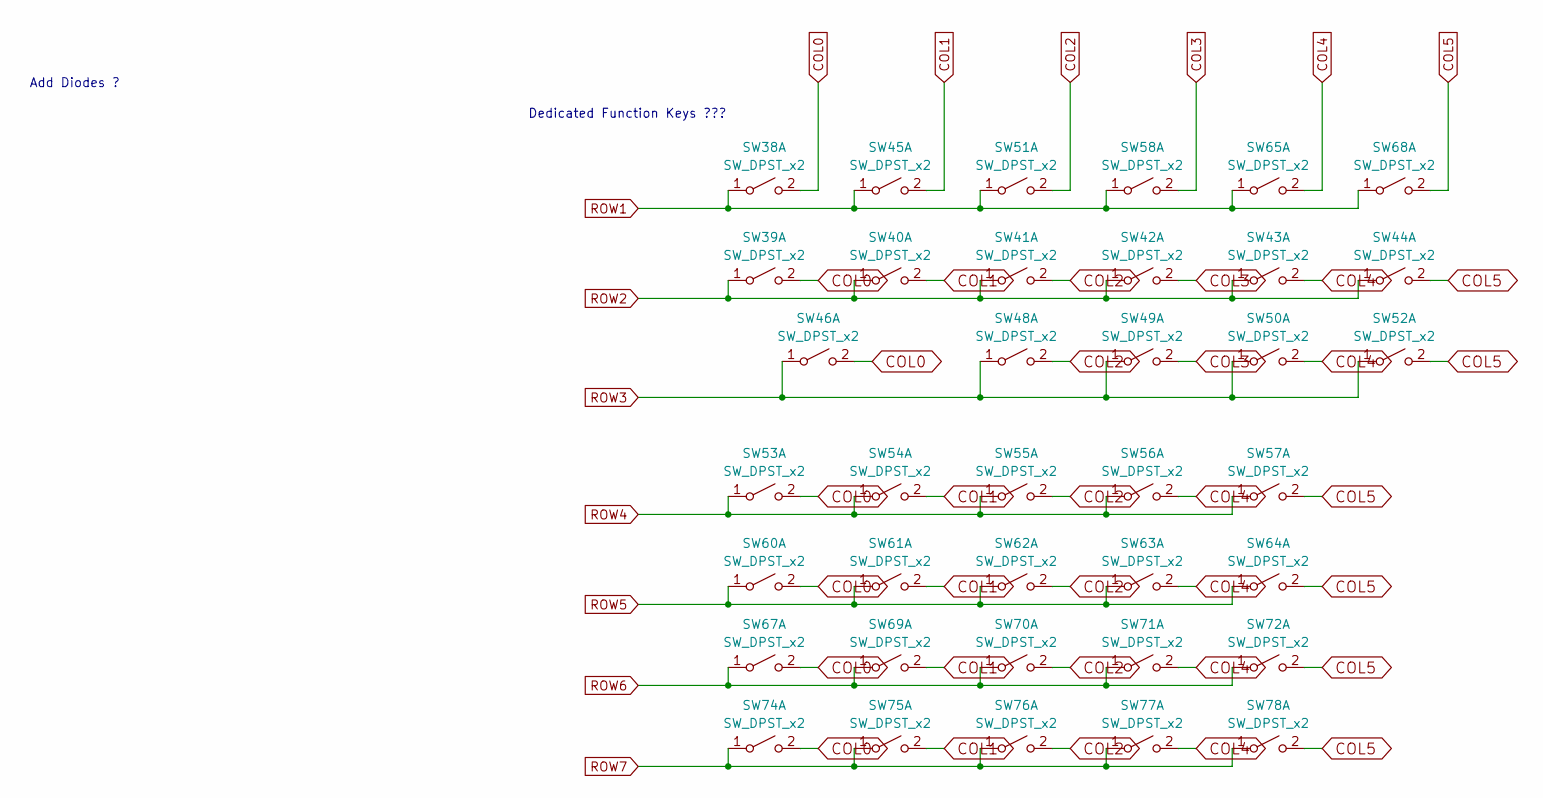
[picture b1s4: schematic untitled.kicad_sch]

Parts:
SW38, SW39, SW40, SW41, SW42, SW43, SW44, SW45, SW48, SW49, SW50, SW51, SW52, SW58, SW65, SW68: SW_DPST_x2; SW_Kailh_Choc_V1_1.00u
SW46: SW_DPST_x2; SW_Kailh_Choc_V1_2.00u
SW53, SW54, SW55, SW56, SW57, SW60, SW61, SW62, SW63, SW64, SW67, SW69, SW70, SW71, SW72, SW74, SW75, SW76, SW77, SW78: SW_DPST_x2; SW_Kailh_Choc_V1_1.25u

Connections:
COL0: SW38.2 (B), SW39.2 (B), SW46.2 (B), SW53.2 (B), SW60.2 (B), SW67.2 (B), SW74.2 (B); also elsewhere on the board
COL1: SW40.2 (B), SW45.2 (B), SW54.2 (B), SW61.2 (B), SW69.2 (B), SW75.2 (B); also elsewhere on the board
COL2: SW41.2 (B), SW48.2 (B), SW51.2 (B), SW55.2 (B), SW62.2 (B), SW70.2 (B), SW76.2 (B); also elsewhere on the board
COL3: SW42.2 (B), SW49.2 (B), SW58.2 (B); also elsewhere on the board
COL4: SW43.2 (B), SW50.2 (B), SW56.2 (B), SW63.2 (B), SW65.2 (B), SW71.2 (B), SW77.2 (B); also elsewhere on the board
COL5: SW44.2 (B), SW52.2 (B), SW57.2 (B), SW64.2 (B), SW68.2 (B), SW72.2 (B), SW78.2 (B); also elsewhere on the board
ROW1: SW38.1 (A), SW45.1 (A), SW51.1 (A), SW58.1 (A), SW65.1 (A), SW68.1 (A); also elsewhere on the board
ROW2: SW39.1 (A), SW40.1 (A), SW41.1 (A), SW42.1 (A), SW43.1 (A), SW44.1 (A); also elsewhere on the board
ROW3: SW46.1 (A), SW48.1 (A), SW49.1 (A), SW50.1 (A), SW52.1 (A); also elsewhere on the board
ROW4: SW53.1 (A), SW54.1 (A), SW55.1 (A), SW56.1 (A), SW57.1 (A); also elsewhere on the board
ROW5: SW60.1 (A), SW61.1 (A), SW62.1 (A), SW63.1 (A), SW64.1 (A); also elsewhere on the board
ROW6: SW67.1 (A), SW69.1 (A), SW70.1 (A), SW71.1 (A), SW72.1 (A); also elsewhere on the board
ROW7: SW74.1 (A), SW75.1 (A), SW76.1 (A), SW77.1 (A), SW78.1 (A); also elsewhere on the board

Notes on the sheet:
Dedicated Function Keys ???
Add Diodes ?

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
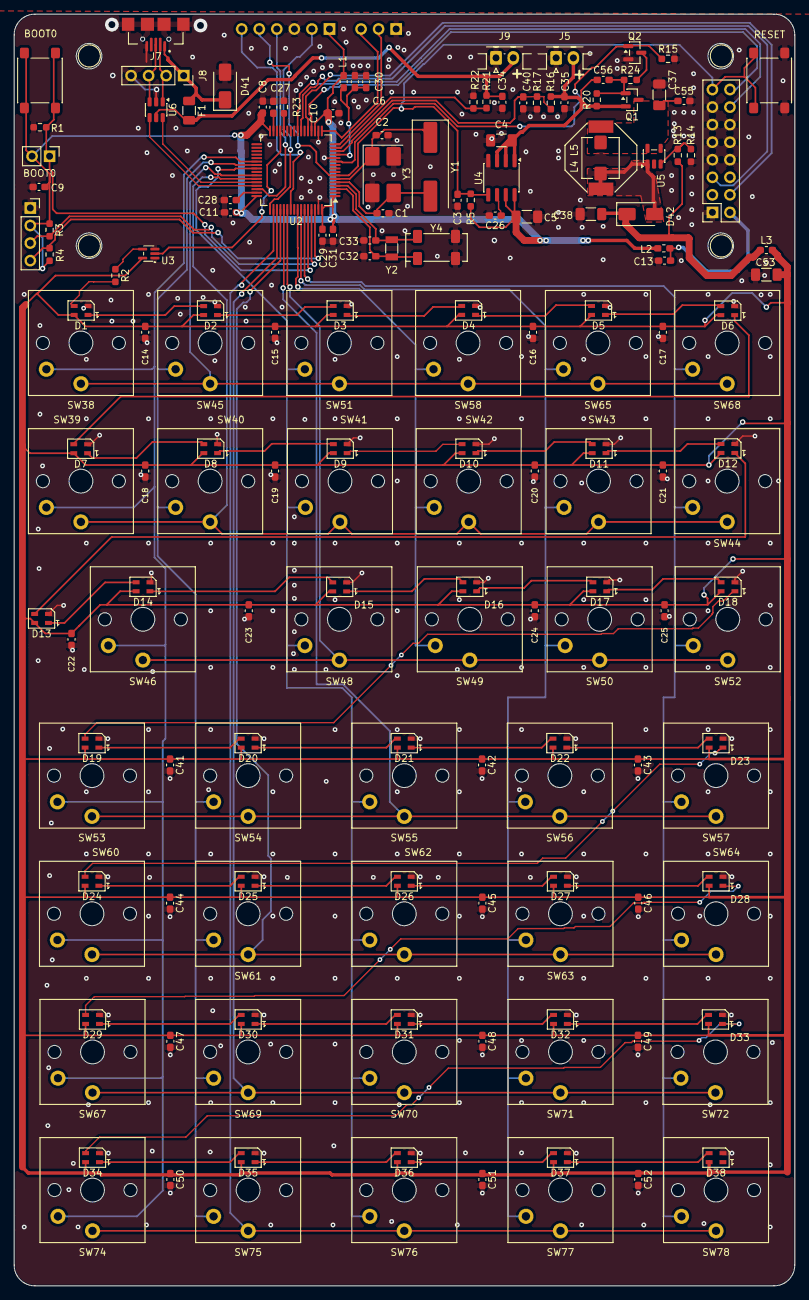
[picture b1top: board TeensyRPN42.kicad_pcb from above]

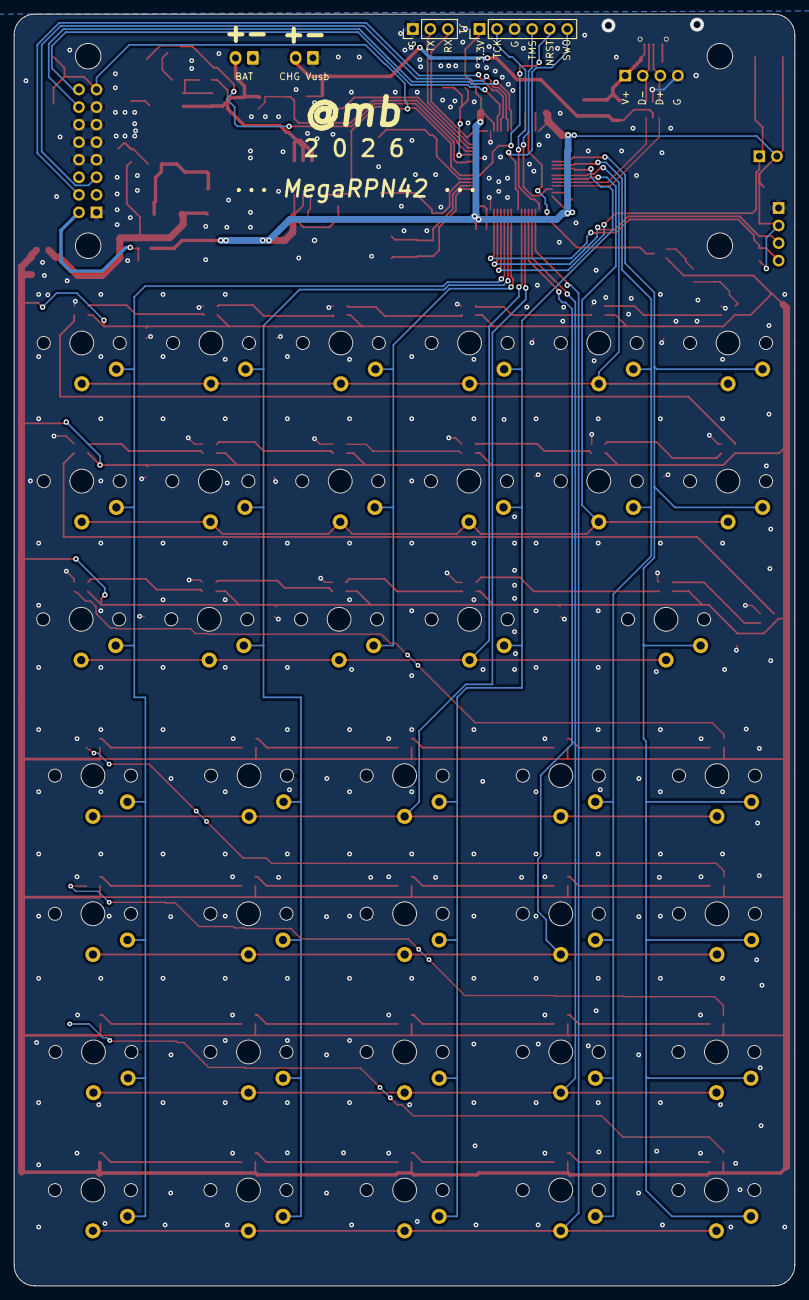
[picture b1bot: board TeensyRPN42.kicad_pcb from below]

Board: 2 copper layers, 113.0 x 184.1 mm, 175 parts (2 on the bottom side), 95 nets.

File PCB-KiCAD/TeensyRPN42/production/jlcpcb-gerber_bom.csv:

Designator,Footprint,Quantity,Value,LCSC Part #
"C1, C2",0603,2,18pF,
"C10, C11, C13, C14, C15, C16, C17, C18, C19, C20, C21, C22, C23, C24, C25, C29, C3, C40, C41, C42, C43, C44, C45, C46, C47, C48, C49, C50, C51, C52, C55, C56, C6, C8, C9",0603,35,100nF,
C26,0603,1,1nF,
"C27, C28, C30, C31, C34, C35",0603,6,2.2uF,
"C32, C33",0603,2,6.8pF,
"C37, C38, C4, C5, C53",1206,5,22uF,
"D1, D10, D11, D12, D13, D14, D15, D16, D17, D18, D19, D2, D20, D21, D22, D23, D24, D25, D26, D27, D28, D29, D3, D30, D31, D32, D33, D34, D35, D36, D37, D38, D4, D5, D6, D7, D8, D9",LED_SK6805_PLCC4_2.4x2.7mm_P1.3mm,38,SK6805,
D41,D_SMA,1,SMAJ5.0A,
D42,D_SMA,1,SS34,
F1,1206,1,750mA hold,
J1,PinHeader_1x06_P2.54mm_Vertical,1,SWD,
J10,PinHeader_1x02_P2.54mm_Vertical,1,BOOT0 jumper,
"J2, J8",PinSocket_1x04_P2.54mm_Vertical,2,Conn_01x04,
J3,OLED-2.8inch16pin,1,Conn_02x08_Odd_Even,
J4,PinHeader_1x03_P2.54mm_Vertical,1,Serial,
J5,JST_EH_S2B-EH_1x02_P2.50mm_Horizontal,1,BAT,
J7,USB_Micro-B_Reichelt_MIC-USB-BBU,1,USB_B_Micro,
J9,JST_EH_S2B-EH_1x02_P2.50mm_Horizontal,1,CHG Vusb,
L1,0603,1,600R@100MHz 0.5A,
"L2, L3",0603,2,600R@100MHz 1.3A,
L4,L_Bourns_SRP5030T,1,6.3uH,
L5,L_Bourns-SRU1028_10.0x10.0mm,1,10uH,
Q1,SOT-23,1,IRLML6401,
Q2,SOT-23,1,2N7002,
"R1, R23, R24, R5",0603,4,10k,
R13,0603,1,66.5k,
R14,0603,1,22k,
"R15, R20, R21",0603,3,100k,
"R16, R17",0603,2,200k,
R2,0603,1,470,
R22,0603,1,150k,
"R3, R4",0603,2,2.2k,
"SW1, SW2",SW_SPST_PTS645Sx43SMTR92,2,SW_Push_Dual,
"SW38, SW39, SW40, SW41, SW42, SW43, SW44, SW45, SW48, SW49, SW50, SW51, SW52, SW58, SW65, SW68",SW_Kailh_Choc_V1_1.00u,16,SW_DPST_x2,
SW46,SW_Kailh_Choc_V1_2.00u,1,SW_DPST_x2,
"SW53, SW54, SW55, SW56, SW57, SW60, SW61, SW62, SW63, SW64, SW67, SW69, SW70, SW71, SW72, SW74, SW75, SW76, SW77, SW78",SW_Kailh_Choc_V1_1.25u,20,SW_DPST_x2,
U2,LQFP-64_10x10mm_P0.5mm,1,STM32F405RGTx,
U3,SOT-353_SC-70-5,1,74!AHCT!125,
U4,SOIC-8_3.9x4.9mm_P1.27mm,1,MCP1727-3302xSN,
U5,SOT-23-5,1,TS1935BCX5,
U6,SOT-23-6,1,USBLC6-2SC6,
Y1,Crystal_SMD_HC49-SD,1,Crystal 8MHz,
Y2,Crystal_SMD_3215-2Pin_3.2x1.5mm,1,32.768kHz CL6pF,
Y3,Crystal_SMD_0603-4Pin_6.0x3.5mm_HandSoldering,1,8MHz 12pF,
Y4,Crystal_SMD_IQD_85SMX-4Pin_8.7x3.7mm,1,32.768kHz 85SMX (alt. Y2),

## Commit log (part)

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2024-03-08 Typo..
2024-03-12 Some optimizations..
2024-03-12 Trying console app..
2025-07-18 copied console app for reference.
2025-07-30 Added local
2025-07-31 stm32 test
2025-07-31 fix merge
2025-07-31 going native...
2025-11-09 Added KeyChoc stuff
2025-11-10 removed printfs
2025-11-10 Cleanup
2025-11-11 DebugStuff
2025-11-14 experiments with intel lib
2025-11-18 Oh signs of live with double preci
2025-11-18 A little PCBing
2025-11-22 more PCB
2026-02-06 more pcb ...
2026-02-12 kram
2026-02-12 More README...
2026-03-16 readme...
